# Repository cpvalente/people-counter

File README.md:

# people-counter

  People Counter - Sender Node

  Program detects events from PIR sensor and sends and counter over i2c <br />
  Programmed to be paired with people-seven code <br />
  Programmed to run on Adafruit Adalogger 32u4 <br />

  ### TO-DO

 ```
  - Add file header
  - Make BOM
 ```

  ### Implemented

 ```
  - Send I2C information to displays
  - SD operations
  -- Log CSV (a bit silly without RTC, implemented anyway)
  -- Read value from SD if it exists
  - Serial for debug and comm
  - Value from digitalInterrupt
  - Handling timing rollover
 ```

  ### Extend

 ```
  - Better handle interval between measurements
  - DEBUG mode
  - Add RTC
  - Communications, see AdaLight https://github.com/adafruit/Adalight/blob/master/Arduino/LEDstream/LEDstream.pde
 ```

  ### NOTES

 ```
  Serial Events not working with adalogger
  Events have noInterrupt()
  Arduino SD library returned false readings after certain number of entries (~400)
 ```

  ### License

  This project is licensed under the MIT License - see the [LICENSE.md](LICENSE.md) file for details

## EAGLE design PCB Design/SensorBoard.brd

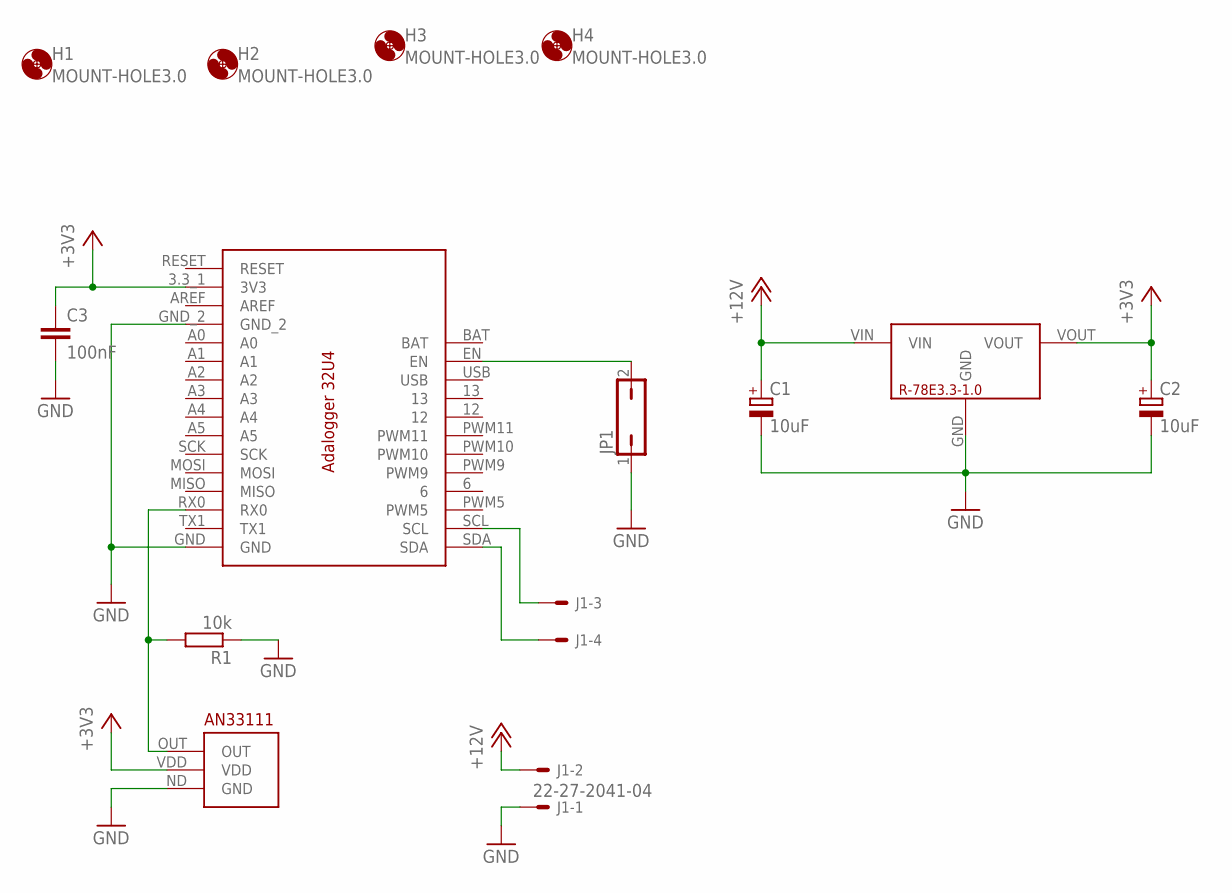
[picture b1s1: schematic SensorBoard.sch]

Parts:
C1, C2: 10uF; E2,5-7
C3: 100nF; C050-025X075
H1, H2, H3, H4: MOUNT-HOLE3.0; 3,0
J1: 22-27-2041-04; 6410-04
JP1: JP1Q; JP1
R1: 10k; 0207/7
U$1: ADALOGGER_32U4_BOARD
U$2: AMN33111; AN33111
U$3: R-78E3.3-1.0

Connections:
+3V3: C2.+, C3.1, U$1.3.3_1 (3V3), U$2.VDD, U$3.VOUT
+12V: C1.+, J1.2, U$3.VIN
GND: C1.-, C2.-, C3.2, J1.1, JP1.1, R1.1, U$1.GND, U$1.GND_2, U$2.ND (GND), U$3.GND
unnamed: R1.2, U$1.RX0, U$2.OUT
unnamed: JP1.2, U$1.EN
SCL: J1.3, U$1.SCL
SDA: J1.4, U$1.SDA

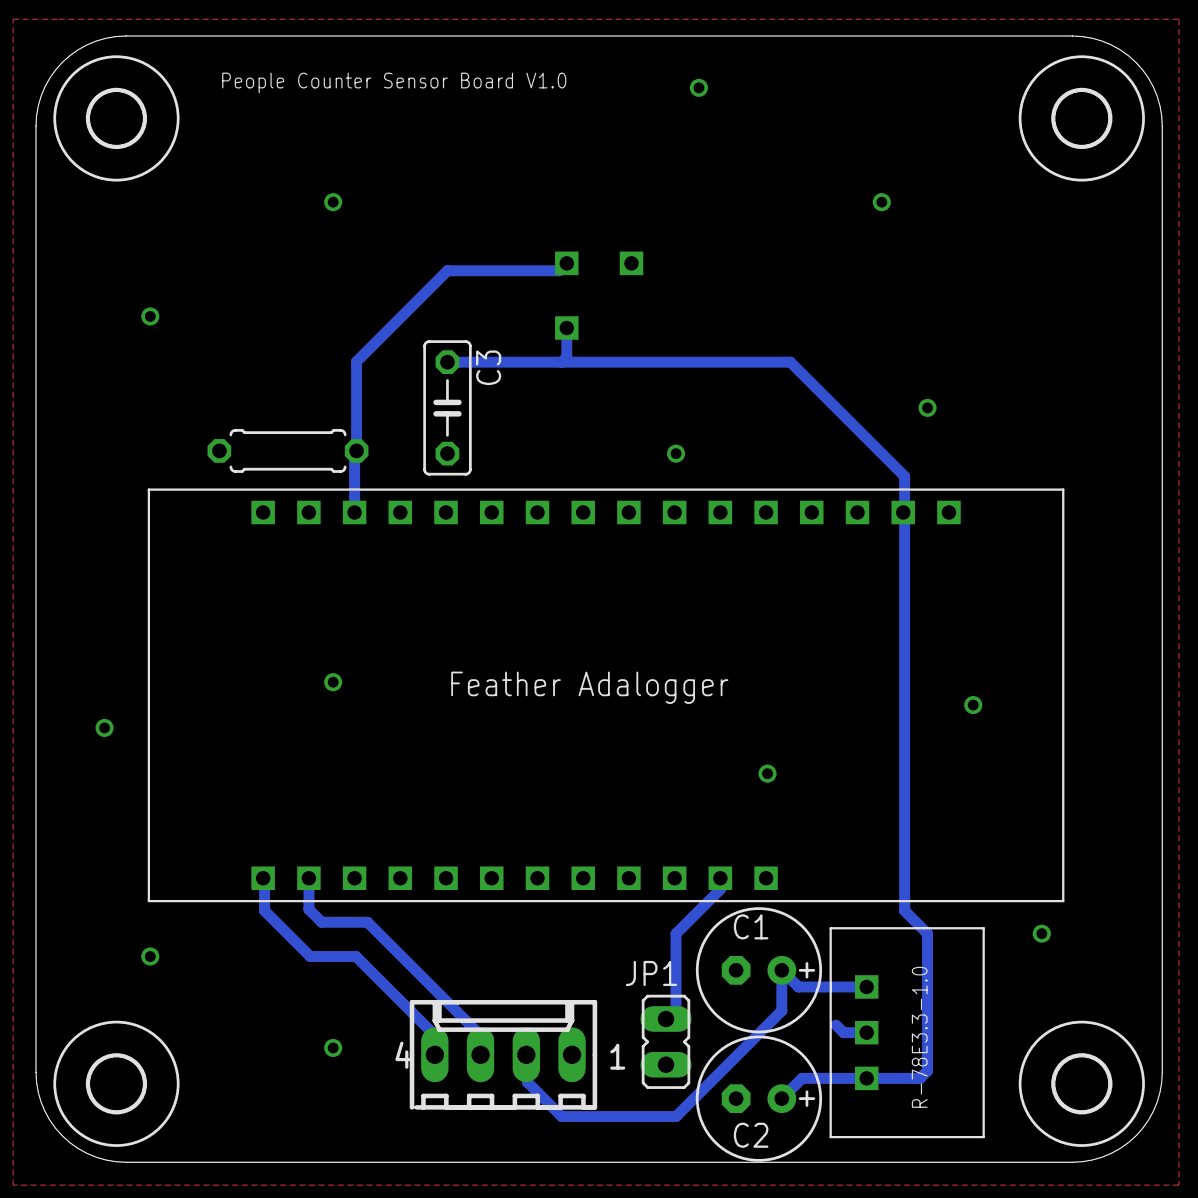
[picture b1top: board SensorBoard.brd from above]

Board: 2 copper layers, 62.6 x 62.6 mm, 13 parts (1 on the bottom side), 7 nets.

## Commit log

2018-03-15 first commit
    Prototyping stage code
    Functional but untested
2018-03-18 fixed timing rollover issues
2018-03-21 interrupts, untested
2018-03-24 SD logging
2018-03-25 readme
2018-03-25 readme formatting
2018-03-25 disliking markdown
2018-04-20 bug fixes
    separed into multiple files
2018-04-20 enclosure design
2018-04-21 small improvements
2018-04-22 Initial Commit
    PCB Design for sensor + feather
